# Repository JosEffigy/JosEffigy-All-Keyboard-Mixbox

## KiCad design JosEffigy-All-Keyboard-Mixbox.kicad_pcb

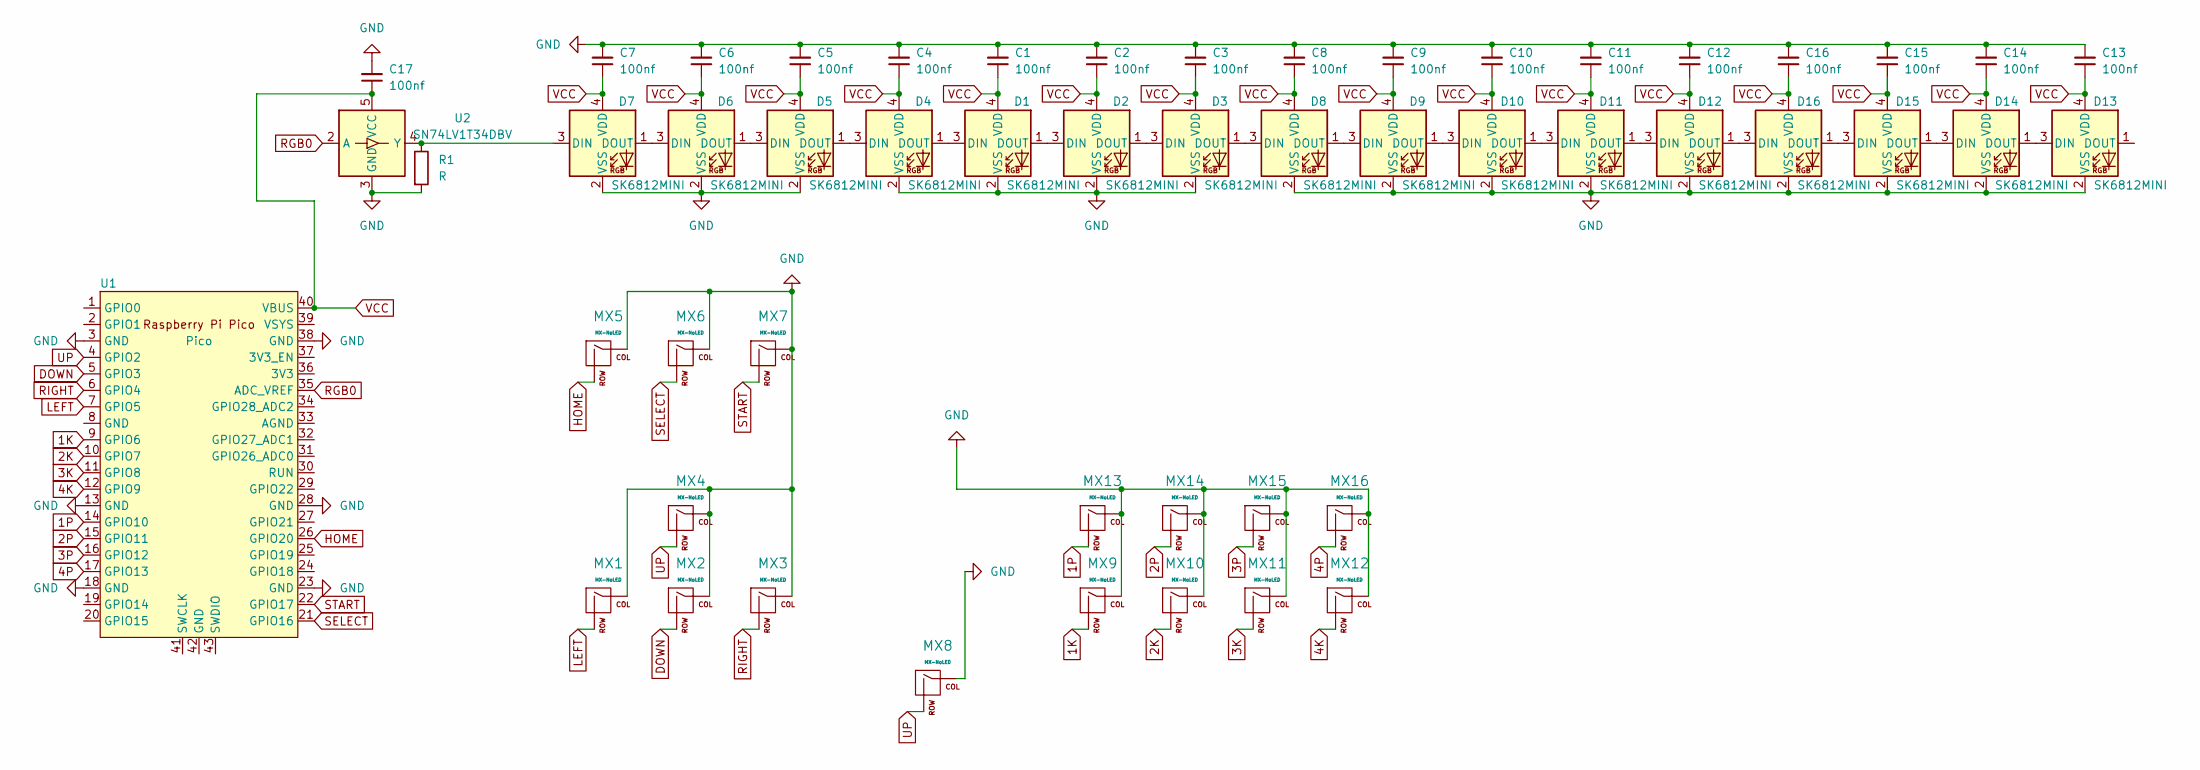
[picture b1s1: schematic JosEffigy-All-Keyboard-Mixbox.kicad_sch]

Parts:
C1, C2, C3, C4, C5, C6, C7, C8, C9, C10, C11, C12, C13, C14, C15, C16, C17: 100nf; CAPC1005X55N
D1, D2, D3, D4, D5, D6, D7, D8, D9, D10, D11, D12, D13, D14, D15, D16: SK6812MINI; YS-SK6812MINI-E
MX1, MX2, MX3, MX4, MX5, MX6, MX7, MX9, MX10, MX11, MX12, MX13, MX14, MX15, MX16: MX-NoLED; SW_Hotswap_Kailh_MX_Plated_1.00u
MX8: MX-NoLED; SW_Hotswap_Kailh_MX_Plated_2.00u
R1: R; R_0402_1005Metric
U1: Pico; RPi_Pico_SMD_TH
U2: SN74LV1T34DBV; SOT-23-5

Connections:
1K: MX9.2 (ROW), U1.9 (GPIO6)
1P: MX13.2 (ROW), U1.14 (GPIO10)
2K: MX10.2 (ROW), U1.10 (GPIO7)
2P: MX14.2 (ROW), U1.15 (GPIO11)
3K: MX11.2 (ROW), U1.11 (GPIO8)
3P: MX15.2 (ROW), U1.16 (GPIO12)
4K: MX12.2 (ROW), U1.12 (GPIO9)
4P: MX16.2 (ROW), U1.17 (GPIO13)
DOWN: MX2.2 (ROW), U1.5 (GPIO3)
GND: C1.2, C2.2, C3.2, C4.2, C5.2, C6.2, C7.2, C8.2, C9.2, C10.2, C11.2, C12.2, C13.2, C14.2, C15.2, C16.2, C17.2, D1.2 (VSS), D2.2 (VSS), D3.2 (VSS), D4.2 (VSS), D5.2 (VSS), D6.2 (VSS), D7.2 (VSS), D8.2 (VSS), D9.2 (VSS), D10.2 (VSS), D11.2 (VSS), D12.2 (VSS), D13.2 (VSS), D14.2 (VSS), D15.2 (VSS), D16.2 (VSS), MX1.1 (COL), MX2.1 (COL), MX3.1 (COL), MX4.1 (COL), MX5.1 (COL), MX6.1 (COL), MX7.1 (COL), MX8.1 (COL), MX9.1 (COL), MX10.1 (COL), MX11.1 (COL), MX12.1 (COL), MX13.1 (COL), MX14.1 (COL), MX15.1 (COL), MX16.1 (COL), R1.2, U1.3 (GND), U1.13 (GND), U1.18 (GND), U1.23 (GND), U1.28 (GND), U1.38 (GND), U2.3 (GND)
HOME: MX5.2 (ROW), U1.26 (GPIO20)
LEFT: MX1.2 (ROW), U1.7 (GPIO5)
unnamed: D1.3 (DIN), D4.1 (DOUT)
unnamed: D1.1 (DOUT), D2.3 (DIN)
unnamed: D2.1 (DOUT), D3.3 (DIN)
unnamed: D3.1 (DOUT), D8.3 (DIN)
unnamed: D4.3 (DIN), D5.1 (DOUT)
unnamed: D5.3 (DIN), D6.1 (DOUT)
unnamed: D6.3 (DIN), D7.1 (DOUT)
unnamed: D7.3 (DIN), R1.1, U2.4 (Y)
unnamed: D8.1 (DOUT), D9.3 (DIN)
unnamed: D9.1 (DOUT), D10.3 (DIN)
unnamed: D10.1 (DOUT), D11.3 (DIN)
unnamed: D11.1 (DOUT), D12.3 (DIN)
unnamed: D12.1 (DOUT), D16.3 (DIN)
unnamed: D13.3 (DIN), D14.1 (DOUT)
unnamed: D14.3 (DIN), D15.1 (DOUT)
unnamed: D15.3 (DIN), D16.1 (DOUT)
RGB0: U1.35 (ADC_VREF), U2.2 (A)
RIGHT: MX3.2 (ROW), U1.6 (GPIO4)
SELECT: MX6.2 (ROW), U1.21 (GPIO16)
START: MX7.2 (ROW), U1.22 (GPIO17)
UP: MX4.2 (ROW), MX8.2 (ROW), U1.4 (GPIO2)
VCC: C1.1, C2.1, C3.1, C4.1, C5.1, C6.1, C7.1, C8.1, C9.1, C10.1, C11.1, C12.1, C13.1, C14.1, C15.1, C16.1, C17.1, D1.4 (VDD), D2.4 (VDD), D3.4 (VDD), D4.4 (VDD), D5.4 (VDD), D6.4 (VDD), D7.4 (VDD), D8.4 (VDD), D9.4 (VDD), D10.4 (VDD), D11.4 (VDD), D12.4 (VDD), D13.4 (VDD), D14.4 (VDD), D15.4 (VDD), D16.4 (VDD), U1.40 (VBUS), U2.5 (VCC)

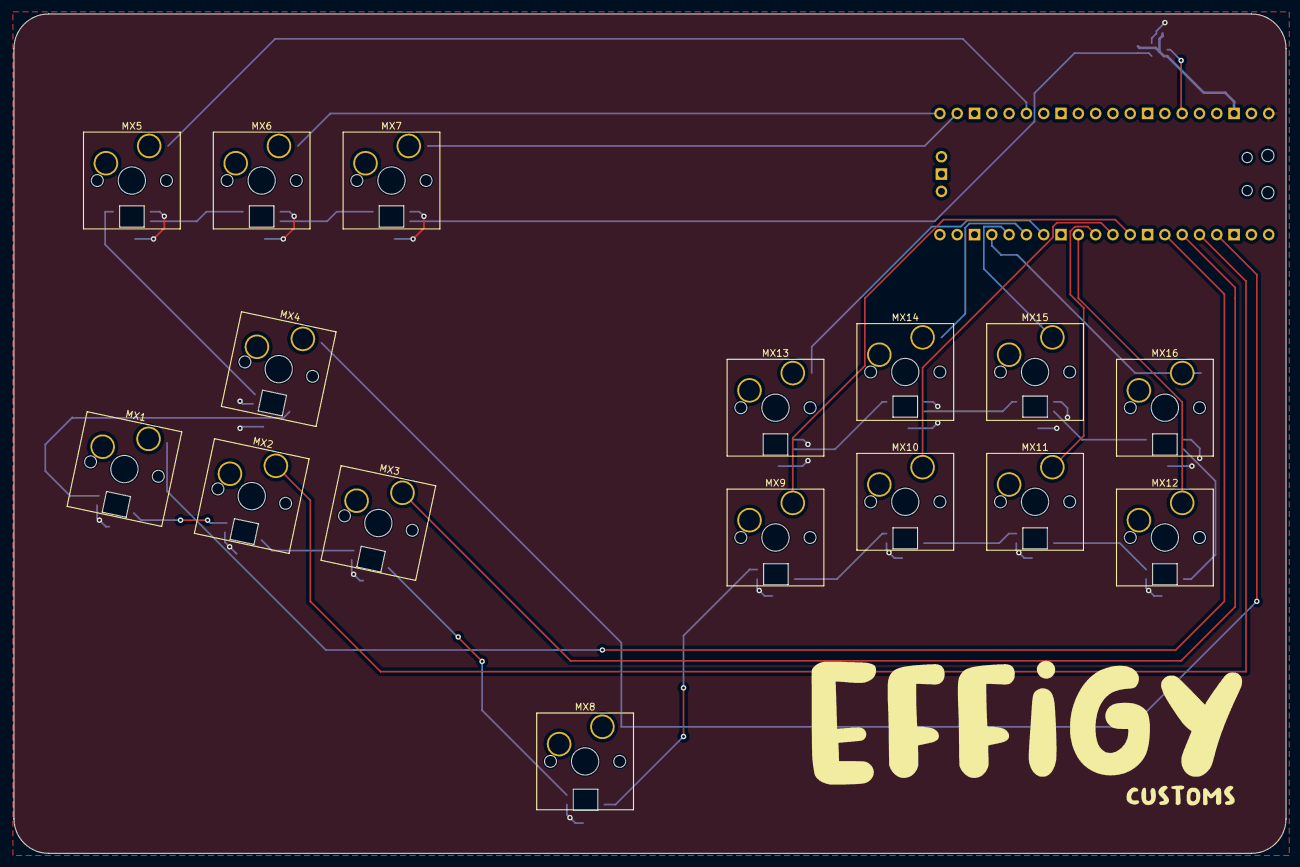
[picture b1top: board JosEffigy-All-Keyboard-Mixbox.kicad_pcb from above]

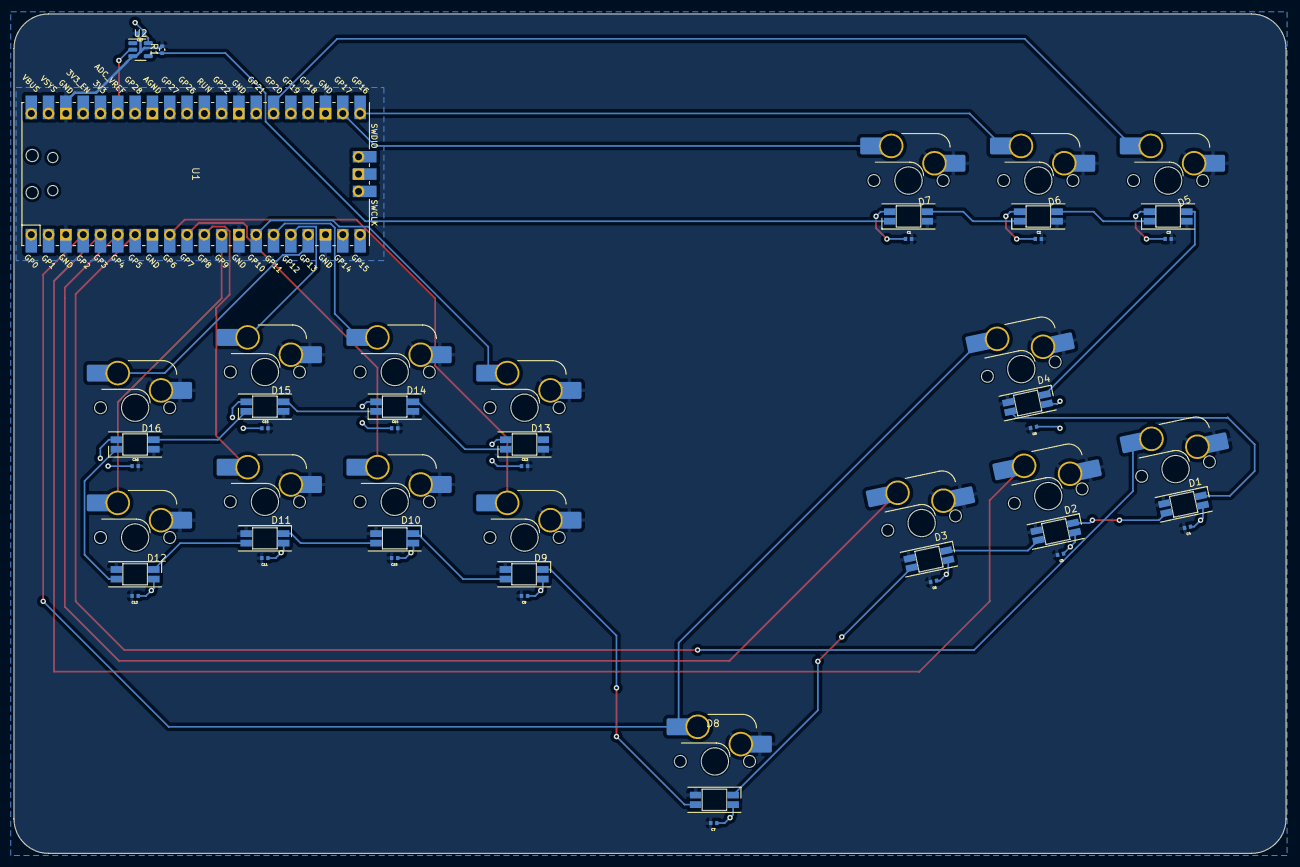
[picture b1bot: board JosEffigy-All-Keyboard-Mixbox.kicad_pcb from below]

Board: 2 copper layers, 186.7 x 123.2 mm, 52 parts (36 on the bottom side), 34 nets.

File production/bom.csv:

Designator,Footprint,Quantity,Value,LCSC Part #
"C1, C10, C11, C12, C13, C14, C15, C16, C17, C2, C3, C4, C5, C6, C7, C8, C9",CAPC1005X55N,17,100nf,
"D1, D10, D11, D12, D13, D14, D15, D16, D2, D3, D4, D5, D6, D7, D8, D9",YS-SK6812MINI-E,16,SK6812MINI,
"MX1, MX10, MX11, MX12, MX13, MX14, MX15, MX16, MX2, MX3, MX4, MX5, MX6, MX7, MX9",SW_Hotswap_Kailh_MX_Plated_1.00u,15,MX-NoLED,
MX8,SW_Hotswap_Kailh_MX_Plated_2.00u,1,MX-NoLED,
R1,0402,1,R,
U1,RPi_Pico_SMD_TH,1,Pico,
U2,SOT-23-5,1,SN74LV1T34DBV,

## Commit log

2023-06-05 Initialize Project
2023-06-05 Add submodules
2023-06-05 Add submodule RP2040
2023-06-05 Lib table and Sym table update
2023-06-05 Added Schematic
2023-06-05 Giga Update - PCB Almost complete
    To Do: Holes, Fix Silkscreen, gerber
2023-06-06 Release 1.0
2023-06-06 Release 1.0b
    Moved power to VBUS, added DTranslator, added Capacitors
2023-06-06 Release 1.0c
    redid the routing
2023-06-07 Release 1.0d
    I think It's ready
2023-06-07 Release 1.0d
    re-commit, added
    production folder
2023-06-07 Release 1.0e
    reupload pcb files
2023-06-07 Release 1.1
2023-06-09 Release 1.2
    Forgot to rotate movement keys.
2023-06-09 Release 1.1b
    Update just to be sure
2023-06-09 Redid all routing manually
